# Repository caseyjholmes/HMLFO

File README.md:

# HMLFO
Holmes Modular 2HP Eurorack Module Version of Niklas Rohnnberg's Analog LFO.. with PSI Power 

These are simple board files for a PCB and a panel for a small analog 2HP Eurorack format synthesizer LFO Module with reversible power input. 
Just print yourself some PCB's and add the parts then adjust the trimmer while you connect the outputs to an oscilloscope to calibrate. 

Build Notes:
If the trim pot isn't adjusted right, the circuit won't run properly. Don't be scared if it doesn't cycle intiailly. It needs calibration. Hook the outputs to an oscilloscope and mess with the trim pot. You can get 5 - 10V operation if you tune it some.

Use MTS-102 switches on ebay. You'll need to file down the tiny plastic nubs on the botton with a needle file to get the switches to fit at the same height as the jacks and pots, but it is very much possible. 

BE SURE TO PAY SPECIAL ATTENTION TO THE VALUES OF THE POTENTIOMETERS. YOU HAVE BEEN WARNED! 

You may change C1 and C5 to adjust the LFO rates that are selectable via the switch. 
Enjoy!
-Casey

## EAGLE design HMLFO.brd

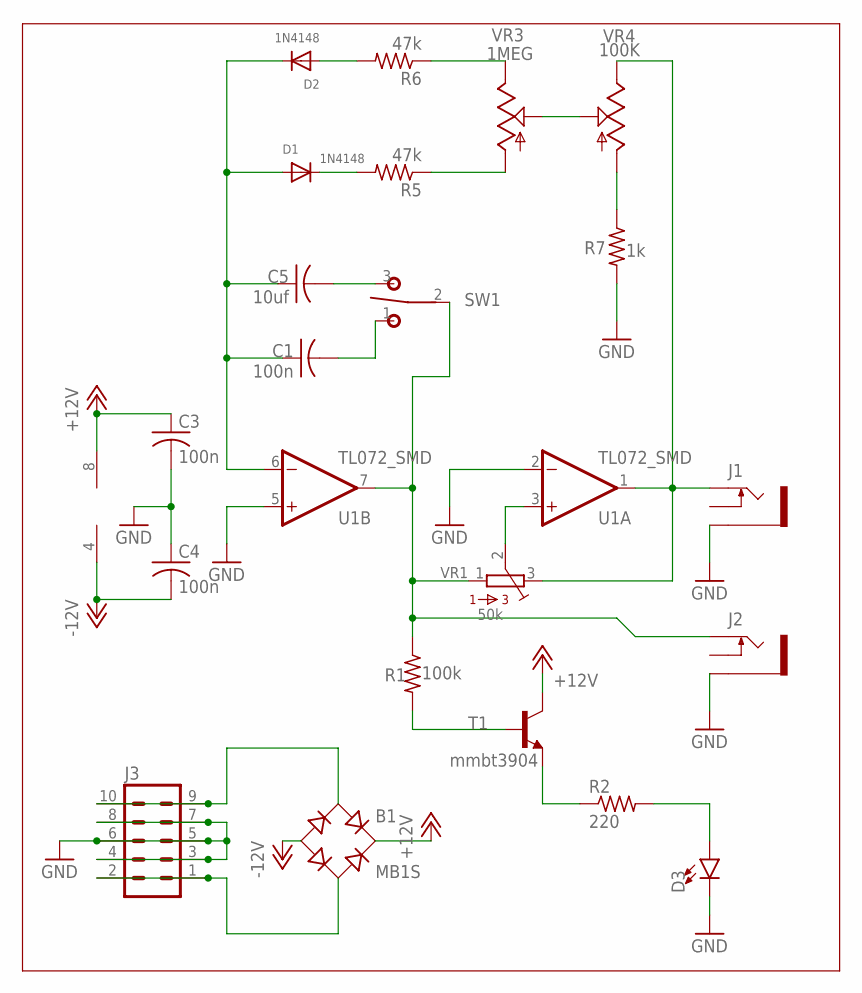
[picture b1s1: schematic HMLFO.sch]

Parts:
B1: MB1S; SOIC-4
C1, C3, C4: 100n; C0603K
C5: 10uf; C0805K
D1, D2: 1N4148; SOD-323F
D3: LED3MM; LED_3MM
J1, J2: THONKICONNNEW; WQP-PJ301M-12_JACK
J3: MA05-2
R1: 100k; R0603
R2: 220; R0603
R5, R6: 47k; R0603
R7: 1k; R0603
SW1: T-80-T-SPDT-ON-OFF-ON; M9040P
T1: mmbt3904; SOT23-BEC
U1: TL072_SMD; SO08
VR1: 50k; BOURNS_3362P_TRIMMER
VR3: 1MEG; 9MM_SNAP-IN_POT
VR4: 100K; 9MM_SNAP-IN_POT

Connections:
+12V: B1.+, C3.1, T1.C, U1.8 (V+)
-12V: B1.-, C4.2, U1.4 (V-)
GND: C3.2, C4.1, D3.K (C), J1.P$3_SLEEVE (SLEEVE), J2.P$3_SLEEVE (SLEEVE), J3.3, J3.4, J3.5, J3.6, J3.7, J3.8, R7.2, U1.2 (-IN), U1.5 (+IN)
unnamed: C1.1, C5.1, D1.A, D2.C, U1.6 (-IN)
unnamed: VR3.2 (S), VR4.2 (S)
unnamed: R6.1, VR3.3 (E)
unnamed: R5.1, VR3.1 (A)
unnamed: D1.C, R5.2
unnamed: D2.A, R6.2
unnamed: U1.3 (+IN), VR1.2
unnamed: J2.P$1_TIP (TIP), R1.1, SW1.2, U1.7 (OUT), VR1.1
unnamed: J1.P$1_TIP (TIP), U1.1 (OUT), VR1.3, VR4.3 (E)
unnamed: R7.1, VR4.1 (A)
unnamed: R1.2, T1.B
unnamed: R2.1, T1.E
unnamed: D3.A, R2.2
unnamed: C1.2, SW1.1 (O)
unnamed: C5.2, SW1.3 (S)
unnamed: B1.~1 (AC1), J3.9, J3.10
unnamed: B1.~2 (AC2), J3.1, J3.2

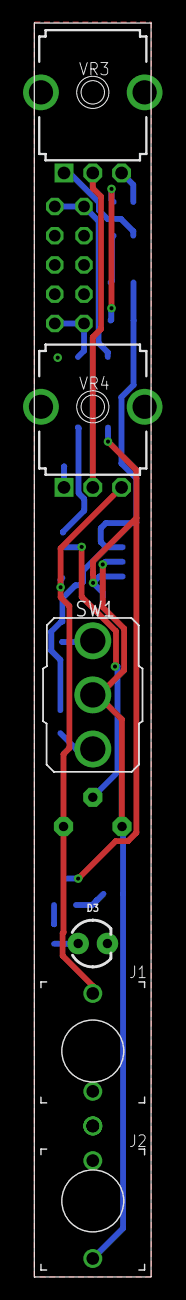
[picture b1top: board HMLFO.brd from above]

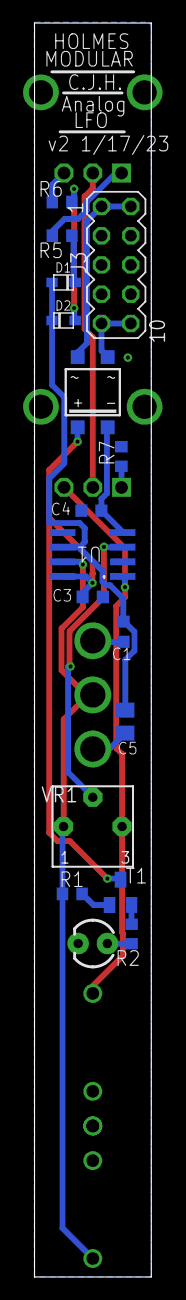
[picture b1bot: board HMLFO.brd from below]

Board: 2 copper layers, 10.1 x 108.9 mm, 22 parts (16 on the bottom side), 20 nets.

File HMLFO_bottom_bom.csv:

Comment,Designator,Footprint,LCSC Part #
1N4148,D1 D2,SOD-323F,
1k,R7,R0603,
10uf,C5,C0805K,
47k,R5 R6,R0603,
100k,R1,R0603,
100n,C1 C3 C4,C0603K,
220,R2,R0603,
MB1S,B1,SOIC-4,
TL072_SMD,U1,SO08,
mmbt3904,T1,SOT23-BEC,

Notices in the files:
parts and their libraries:
SparkFun-LED: Licensing: Creative Commons ShareAlike 4.0 International - https://creativecommons.org/licenses/by-sa/4.0
